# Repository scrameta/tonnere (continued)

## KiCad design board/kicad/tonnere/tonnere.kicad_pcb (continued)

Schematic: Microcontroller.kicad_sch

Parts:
BT1: CR2032; BAT-TH_BS-05-A1BJ001; Manufacturer Part BS-05-A1BJ001; JLC_3DModel 65806d021c214524b18c90626aa24a1f
C11, C21, C31, C33, C35, C36, C37, C41, C45, C54, C58, C63, C68, C70: 0.1uF; C_0603_1608Metric; LCSC C14663
C16, C19: 22pF; C_0603_1608Metric; LCSC C1653
C17, C18: 16pF; C_0603_1608Metric; LCSC C327125
C22, C23, C50: 4.7uF; C_0603_1608Metric; LCSC C19666
C25, C26: 18pF; C_0603_1608Metric; LCSC C1647
C29: 1uF; C_0805_2012Metric; LCSC C28323
C66, C67: 2.2uF; C_0603_1608Metric; LCSC C23630
D6: 1N4148WS; D_SOD-323; LCSC C2128
FB1: 70@100MHz; L_0805_2012Metric; LCSC C1012
J8: STM GPIO; PinSocket_1x07_P2.54mm_Vertical; LCSC C225482
J9: STM SWD; PinHeader_1x05_P2.54mm_Vertical; LCSC C225480
J26: I2C; PinHeader_2x02_P2.54mm_Vertical; LCSC C225517
JP1: STM BOOT0; PinHeader_1x03_P2.54mm_Vertical; LCSC C49257
Q3: 2N7002; SOT-23; LCSC C8545
R4, R5: 5k1; R_0603_1608Metric; LCSC C23186
R7, R57: 1k; R_0603_1608Metric; LCSC C21190
R8, R37, R39: 1m; R_0603_1608Metric; LCSC C22935
R31, R58, R63: 10k; R_0603_1608Metric; LCSC C25804
R42: 12K 1%; R_0603_1608Metric; LCSC C22790
R54: 100k; R_0603_1608Metric; LCSC C25803
R56: 820; R_0603_1608Metric; LCSC C23253
R60: 0; R_0603_1608Metric; LCSC C21189; not fitted
R64, R84, R85: 22; R_0603_1608Metric; LCSC C23345
R68, R69: 4k7; R_0603_1608Metric; LCSC C23162
RN7, RN10: 22; R_Array_Convex_4x0603; LCSC C12008
SW2: USB HS/FS; SW-SMD_MST22D18G2; JLC_3DModel a98562e0d24740e1809e54f73242e180
U5: TPD4E02B04DQA; USON-10_2.5x1.0mm_P0.5mm; LCSC C106794
U12: 74LVC1G17; SOT-23-5; LCSC C7836
U18, U22: FSUSB42UMX-TP; XQFN-10_L1.8-W1.4-P0.40-TL; Manufacturer Part FSUSB42UMX-TP; JLC_3DModel ba08a50be60c45c893f1ed2ee1dbd52d
U21: USB3300-EZK; QFN-32-1EP_5x5mm_P0.5mm_EP3.45x3.45mm; LCSC C108383
U25: STM32F407ZGTx; LQFP-144_20x20mm_P0.5mm; LCSC C36869
U27: PCA9546APWR; TSSOP-16_L5.0-W4.4-P0.65-LS6.4-BL; Manufacturer Part PCA9546APWR; JLC_3DModel 534f03d8fe164fbab551f91e5a792e30
USB2: TYPE-C 14P CC-2.6; TYPE-C-TH_TYPE-C-14P-CC-2.6; MPN TYPE-C 14P CC-2.6; LCSC Part C5187475
Y1: 24MHz; Crystal_SMD_3225-4Pin_3.2x2.5mm; LCSC C5122304
Y2: 8MHz; Crystal_SMD_3225-4Pin_3.2x2.5mm; LCSC C2924617
Y3: 32.768KHz; Crystal_SMD_3215-2Pin_3.2x1.5mm; LCSC C32346

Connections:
+3V3: C31.1, C33.1, C36.1, C41.1, C45.1, C54.1, C58.1, C63.1, C68.1, C70.1, FB1.1, J8.1, J9.1, J26.1, R31.1, R68.1, R69.1, SW2.1 (A), U12.5 (VCC), U18.9 (VCC), U21.6 (VDD3.3), U21.16 (VDD3.3), U21.25 (VDD3.3), U21.30 (VDD3.3), U21.31 (REG_EN), U22.9 (VCC), U25.17 (VDD), U25.30 (VDD), U25.39 (VDD), U25.52 (VDD), U25.62 (VDD), U25.72 (VDD), U25.84 (VDD), U25.95 (VDD), U25.108 (VDD), U25.121 (VDD), U25.131 (VDD), U25.143 (PDR_ON), U25.144 (VDD), U27.16 (VCC); also elsewhere on the board
+3VA3_STM: C29.1, C37.1, FB1.2, U25.32 (VREF+), U25.33 (VDDA); also elsewhere on the board
+5V: SW2.4 (A); also elsewhere on the board
/AtariInterfaces/JOY2.POT4: U25.22 (PF10); also elsewhere on the board
/AtariInterfaces/JOY2.POT5: U25.27 (PC1); also elsewhere on the board
/AtariInterfaces/JOY2.POT6: U25.34 (PA0); also elsewhere on the board
/AtariInterfaces/JOY2.POT7: U25.35 (PA1); also elsewhere on the board
/AtariInterfaces/JOY.POT0: U25.18 (PF6); also elsewhere on the board
/AtariInterfaces/JOY.POT1: U25.19 (PF7); also elsewhere on the board
/AtariInterfaces/JOY.POT2: U25.20 (PF8); also elsewhere on the board
/AtariInterfaces/JOY.POT3: U25.21 (PF9); also elsewhere on the board
/Audio/STMAUD.ADC.L: U25.42 (PA6); also elsewhere on the board
/Audio/STMAUD.ADC.PBI: U25.44 (PC4); also elsewhere on the board
/Audio/STMAUD.ADC.R: U25.40 (PA4); also elsewhere on the board
/Audio/STMAUD.ADC.SIO: U25.45 (PC5); also elsewhere on the board
/ESP32/ESP.BOOT: U25.91 (PG6); also elsewhere on the board
/ESP32/ESP.EN: U25.92 (PG7); also elsewhere on the board
/ESP32/ESP.SGPI0: U25.93 (PG8); also elsewhere on the board
/ESP32/ESP.SGPI1: U25.124 (PG9); also elsewhere on the board
/ESP32/ESP.SGPI2: U25.125 (PG10); also elsewhere on the board
/ESP32/ESP.SGPIO: U25.100 (PA8); also elsewhere on the board
/ESP32/UART1.RX: U25.97 (PC7); also elsewhere on the board
/ESP32/UART1.TX: U25.96 (PC6); also elsewhere on the board
/FPGA/FPGA.CONFIG_N: U25.128 (PG13); also elsewhere on the board
/FPGA/FPGA.CONF_DONE: U25.132 (PG15); also elsewhere on the board
/FPGA/FPGA.IRQ: U25.127 (PG12); also elsewhere on the board
/FPGA/FPGA.PS_N: U25.126 (PG11); also elsewhere on the board
/FPGA/FPGA.STATUS_N: U25.129 (PG14); also elsewhere on the board
/FPGA/FSMC.A0: U25.10 (PF0); also elsewhere on the board
/FPGA/FSMC.A1: U25.11 (PF1); also elsewhere on the board
/FPGA/FSMC.A2: U25.12 (PF2); also elsewhere on the board
/FPGA/FSMC.A3: U25.13 (PF3); also elsewhere on the board
/FPGA/FSMC.A4: U25.14 (PF4); also elsewhere on the board
/FPGA/FSMC.A5: U25.15 (PF5); also elsewhere on the board
/FPGA/FSMC.A6: U25.50 (PF12); also elsewhere on the board
/FPGA/FSMC.A7: U25.53 (PF13); also elsewhere on the board
/FPGA/FSMC.A8: U25.54 (PF14); also elsewhere on the board
/FPGA/FSMC.A9: U25.55 (PF15); also elsewhere on the board
/FPGA/FSMC.A10: U25.56 (PG0); also elsewhere on the board
/FPGA/FSMC.A11: U25.57 (PG1); also elsewhere on the board
/FPGA/FSMC.A12: U25.87 (PG2); also elsewhere on the board
/FPGA/FSMC.A13: U25.88 (PG3); also elsewhere on the board
/FPGA/FSMC.A14: U25.89 (PG4); also elsewhere on the board
/FPGA/FSMC.A15: U25.90 (PG5); also elsewhere on the board
/FPGA/FSMC.A16: U25.80 (PD11); also elsewhere on the board
/FPGA/FSMC.A17: U25.81 (PD12); also elsewhere on the board
/FPGA/FSMC.A18: U25.82 (PD13); also elsewhere on the board
/FPGA/FSMC.A19: U25.2 (PE3); also elsewhere on the board
/FPGA/FSMC.A20: U25.3 (PE4); also elsewhere on the board
/FPGA/FSMC.A21: U25.4 (PE5); also elsewhere on the board
/FPGA/FSMC.A22: U25.5 (PE6); also elsewhere on the board
/FPGA/FSMC.D0: U25.85 (PD14); also elsewhere on the board
/FPGA/FSMC.D1: U25.86 (PD15); also elsewhere on the board
/FPGA/FSMC.D2: U25.114 (PD0); also elsewhere on the board
/FPGA/FSMC.D3: U25.115 (PD1); also elsewhere on the board
/FPGA/FSMC.D4: U25.58 (PE7); also elsewhere on the board
/FPGA/FSMC.D5: U25.59 (PE8); also elsewhere on the board
/FPGA/FSMC.D6: U25.60 (PE9); also elsewhere on the board
/FPGA/FSMC.D7: U25.63 (PE10); also elsewhere on the board
/FPGA/FSMC.D8: U25.64 (PE11); also elsewhere on the board
/FPGA/FSMC.D9: U25.65 (PE12); also elsewhere on the board
/FPGA/FSMC.D10: U25.66 (PE13); also elsewhere on the board
/FPGA/FSMC.D11: U25.67 (PE14); also elsewhere on the board
/FPGA/FSMC.D12: U25.68 (PE15); also elsewhere on the board
/FPGA/FSMC.D13: U25.77 (PD8); also elsewhere on the board
/FPGA/FSMC.D14: U25.78 (PD9); also elsewhere on the board
/FPGA/FSMC.D15: U25.79 (PD10); also elsewhere on the board
/FPGA/FSMC.NBL0: U25.141 (PE0); also elsewhere on the board
/FPGA/FSMC.NBL1: U25.142 (PE1); also elsewhere on the board
/FPGA/FSMC.NE1: U25.123 (PD7); also elsewhere on the board
/FPGA/FSMC.NOE: U25.118 (PD4); also elsewhere on the board
/FPGA/FSMC.NWAIT: U25.122 (PD6); also elsewhere on the board
/FPGA/FSMC.NWE: U25.119 (PD5); also elsewhere on the board
/FPGA/HDMI.SCL: U27.5 (SC0); also elsewhere on the board
/FPGA/HDMI.SDA: U27.4 (SD0); also elsewhere on the board
/FPGA/PLL.SCL1: U27.10 (SC2); also elsewhere on the board
/FPGA/PLL.SCL2: U27.12 (SC3); also elsewhere on the board
/FPGA/PLL.SDA1: U27.9 (SD2); also elsewhere on the board
/FPGA/PLL.SDA2: U27.11 (SD3); also elsewhere on the board
/FPGA/SPI.CS1: U25.136 (PB6); also elsewhere on the board
/FPGA/SPI.CS2: U25.137 (PB7); also elsewhere on the board
/FPGA/SPI.MISO: U25.134 (PB4); also elsewhere on the board
/FPGA/SPI.MOSI: U25.43 (PA7); also elsewhere on the board
/FPGA/SPI.SCK: R64.2; also elsewhere on the board
/IOCards/SD.CK: RN7.4 (R4.1); also elsewhere on the board
/IOCards/SD.CMD: RN7.1 (R1.1); also elsewhere on the board
/IOCards/SD.D0: RN10.4 (R4.1); also elsewhere on the board
/IOCards/SD.D1: RN10.3 (R3.1); also elsewhere on the board
/IOCards/SD.D2: RN10.2 (R2.1); also elsewhere on the board
/IOCards/SD.D3: RN10.1 (R1.1); also elsewhere on the board
/IOCards/SD.DETECT: RN7.3 (R3.1); also elsewhere on the board
/IOCards/SD.WP: RN7.2 (R2.1); also elsewhere on the board
/Microcontroller/1V8: C22.1, U21.15 (VDD1.8), U21.26 (VDD1.8)
/Microcontroller/1VA8: C23.1, U21.29 (VDDA1.8)
/Microcontroller/+3V_BAT: BT1.1, C35.1, U25.6 (VBAT)
/Microcontroller/+V5_VBUS_FOR_DETECT: R7.1, SW2.6 (C), USB2.A4 (VBUS), USB2.A9 (VBUS), USB2.B4 (VBUS), USB2.B9 (VBUS)
/Microcontroller/BOOT1: R63.1, U25.48 (PB2)
/Microcontroller/NRST: C11.1, J9.5, Q3.3 (D), R31.2, U25.25 (NRST)
/Microcontroller/Net-(C20-Pad1): C21.1, R57.1, U12.4
/Microcontroller/Net-(C49-Pad1): C50.1, R56.2, SW2.5 (B)
/Microcontroller/Net-(J9-Pin_4): J8.4, U25.75 (PB14)
/Microcontroller/Net-(J9-Pin_5): J8.5, U25.76 (PB15)
/Microcontroller/Net-(J9-Pin_6): J8.6, U25.110 (PA15)
/Microcontroller/Net-(J9-Pin_7): J8.7, U25.1 (PE2)
/Microcontroller/Net-(J10-Pin_2): J9.2, U25.105 (PA13)
/Microcontroller/Net-(J10-Pin_3): J9.3, U25.109 (PA14)
/Microcontroller/Net-(J27-Pin_3): J26.3, U27.7 (SC1)
/Microcontroller/Net-(J27-Pin_4): J26.4, U27.6 (SD1)
/Microcontroller/Net-(U17-D+): U5.2 (IO2), U18.1 (D+), USB2.A6 (DP1), USB2.B6 (DP2)
/Microcontroller/Net-(U17-D-): U5.1 (IO1), U18.2 (D-), USB2.A7 (DN1), USB2.B7 (DN2)
/Microcontroller/Net-(U17-SEL): SW2.2 (B), U18.10 (SEL), U22.10 (SEL)
/Microcontroller/Net-(U20-RBIAS): R42.1, U21.32 (RBIAS)
/Microcontroller/Net-(U20-RESET): R60.1, U21.9 (RESET)
/Microcontroller/Net-(U20-VBUS): R56.1, U21.4 (VBUS)
/Microcontroller/Net-(U20-XI): C19.2, R37.2, U21.28 (XI), Y1.1
/Microcontroller/Net-(U20-XO): C16.2, R37.1, U21.27 (XO), Y1.3
/Microcontroller/Net-(U23-PA11): R84.1, U25.103 (PA11)
/Microcontroller/Net-(U23-PA12): R85.1, U25.104 (PA12)
/Microcontroller/Net-(U23-PB3): R64.1, U25.133 (PB3)
/Microcontroller/Net-(U23-PC14): C26.2, U25.8 (PC14), Y3.1
/Microcontroller/Net-(U23-PC15): C25.2, U25.9 (PC15), Y3.2
/Microcontroller/Net-(U23-PH0): C18.2, R39.1, U25.23 (PH0), Y2.3
/Microcontroller/Net-(U23-PH1): C17.2, R39.2, U25.24 (PH1), Y2.1
/Microcontroller/Net-(U23-VCAP_1): C66.1, U25.71 (VCAP_1)
/Microcontroller/Net-(U23-VCAP_2): C67.1, U25.106 (VCAP_2)
/Microcontroller/Net-(USB1-CC1): R4.1, USB2.A5 (CC1)
/Microcontroller/Net-(USB1-CC2): R5.1, USB2.B5 (CC2)
/Microcontroller/STM.I2CRESET: U25.49 (PF11), U27.3 (RESET#)
/Microcontroller/STM.SCL: R69.2, U25.139 (PB8), U27.14 (SCL)
/Microcontroller/STM.SDA: R68.2, U25.140 (PB9), U27.15 (SDA)
/Microcontroller/STMUSB.DM1: R84.2, U18.4 (HSD1-), U22.6 (HSD2-)
/Microcontroller/STMUSB.DM2: U18.6 (HSD2-), U21.8 (DM), U22.4 (HSD1-)
/Microcontroller/STMUSB.DP1: R85.2, U18.5 (HSD1+), U22.7 (HSD2+)
/Microcontroller/STMUSB.DP2: U18.7 (HSD2+), U21.7 (DP), U22.5 (HSD1+)
/Microcontroller/USART1.RX: U25.102 (PA10); also elsewhere on the board
/Microcontroller/USART1.TX: U25.101 (PA9); also elsewhere on the board
/Microcontroller/USB.DM: U22.2 (D-); also elsewhere on the board
/Microcontroller/USB.DP: U22.1 (D+); also elsewhere on the board
/Microcontroller/USBPHY.CLK: U21.14 (CLKOUT), U25.41 (PA5)
/Microcontroller/USBPHY.D0: U21.24 (DATA0), U25.37 (PA3)
/Microcontroller/USBPHY.D1: U21.23 (DATA1), U25.46 (PB0)
/Microcontroller/USBPHY.D2: U21.22 (DATA2), U25.47 (PB1)
/Microcontroller/USBPHY.D3: U21.21 (DATA3), U25.69 (PB10)
/Microcontroller/USBPHY.D4: U21.20 (DATA4), U25.70 (PB11)
/Microcontroller/USBPHY.D5: U21.19 (DATA5), U25.73 (PB12)
/Microcontroller/USBPHY.D6: U21.18 (DATA6), U25.74 (PB13)
/Microcontroller/USBPHY.D7: U21.17 (DATA7), U25.135 (PB5)
/Microcontroller/USBPHY.DIR: U21.12 (DIR), U25.28 (PC2)
/Microcontroller/USBPHY.NXT: U21.11 (NXT), U25.29 (PC3)
/Microcontroller/USBPHY.STP: U21.13 (STP), U25.26 (PC0)
/Microcontroller/unconnected-(J9-Pin_3-Pad3): J8.3
/Microcontroller/unconnected-(U4-IO3-Pad4): U5.4 (IO3)
/Microcontroller/unconnected-(U4-IO4-Pad5): U5.5 (IO4)
/Microcontroller/unconnected-(U4-NC-Pad6): U5.6 (NC)
/Microcontroller/unconnected-(U4-NC-Pad7): U5.7 (NC)
/Microcontroller/unconnected-(U4-NC-Pad9): U5.9 (NC)
/Microcontroller/unconnected-(U4-NC-Pad10): U5.10 (NC)
/Microcontroller/unconnected-(U20-CPEN-Pad3): U21.3 (CPEN)
/Microcontroller/unconnected-(U20-EXTVBUS-Pad10): U21.10 (EXTVBUS)
/Microcontroller/unconnected-(U20-ID-Pad5): U21.5 (ID)
GND: BT1.2, C11.2, C16.1, C17.1, C18.1, C19.1, C22.2, C23.2, C25.1, C26.1, C31.2, C33.2, C35.2, C36.2, C41.2, C45.2, C50.2, C54.2, C58.2, C63.2, C66.2, C67.2, C68.2, C70.2, D6.2 (A), J8.2, J9.4, J26.2, Q3.2 (S), R4.2, R5.2, R8.2, R42.2, R54.2, R58.1, R60.2, R63.2, SW2.3 (C), U5.3 (G), U5.8 (G), U12.3 (GND), U18.3 (GND), U18.8 (OE#), U21.1 (GND), U21.2 (GND), U21.33 (GND), U22.3 (GND), U22.8 (OE#), U25.16 (VSS), U25.36 (PA2), U25.38 (VSS), U25.51 (VSS), U25.61 (VSS), U25.83 (VSS), U25.94 (VSS), U25.107 (VSS), U25.120 (VSS), U25.130 (VSS), U27.1 (A0), U27.2 (A1), U27.8 (GND), U27.13 (A2), USB2.A1 (GND), USB2.A12 (GND), USB2.B1 (GND), USB2.B12 (GND), USB2.SH1, USB2.SH2, Y1.2, Y1.4, Y2.2, Y2.4; also elsewhere on the board
GNDA: C29.2, C37.2, U25.31 (VSSA); also elsewhere on the board
unnamed: C21.2, D6.1 (K), Q3.1 (G), R54.1
unnamed: JP1.1 (A), R58.2
unnamed: JP1.3 (B), R57.2
unnamed: JP1.2 (C), U25.138 (BOOT0)
unnamed: R7.2, R8.1, U12.2
unnamed: RN7.8 (R1.2), U25.116 (PD2)
unnamed: RN7.7 (R2.2), U25.117 (PD3)
unnamed: RN7.6 (R3.2), U25.7 (PC13)
unnamed: RN7.5 (R4.2), U25.113 (PC12)
unnamed: RN10.8 (R1.2), U25.112 (PC11)
unnamed: RN10.7 (R2.2), U25.111 (PC10)
unnamed: RN10.6 (R3.2), U25.99 (PC9)
unnamed: RN10.5 (R4.2), U25.98 (PC8)

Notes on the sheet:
ADCDUMMY
H:D2, L:D1 So H=HS_EXT,LS_HUB L=LS_EXT,HS_HUB
With pull up via 10k to 3.3v
Downstream pull ups on other sheets
Automatic DFU mode on VBUS connect - sends 10ms reset pulse on NSRT on connect.
OK to share with VDAC?

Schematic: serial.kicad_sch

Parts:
J13: STM USART TTL; PinSocket_1x03_P2.54mm_Vertical; LCSC C49257

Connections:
/Microcontroller/USART1.RX: J13.3; also elsewhere on the board
/Microcontroller/USART1.TX: J13.2; also elsewhere on the board
GND: J13.1; also elsewhere on the board

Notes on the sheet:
TTL USART for debugging

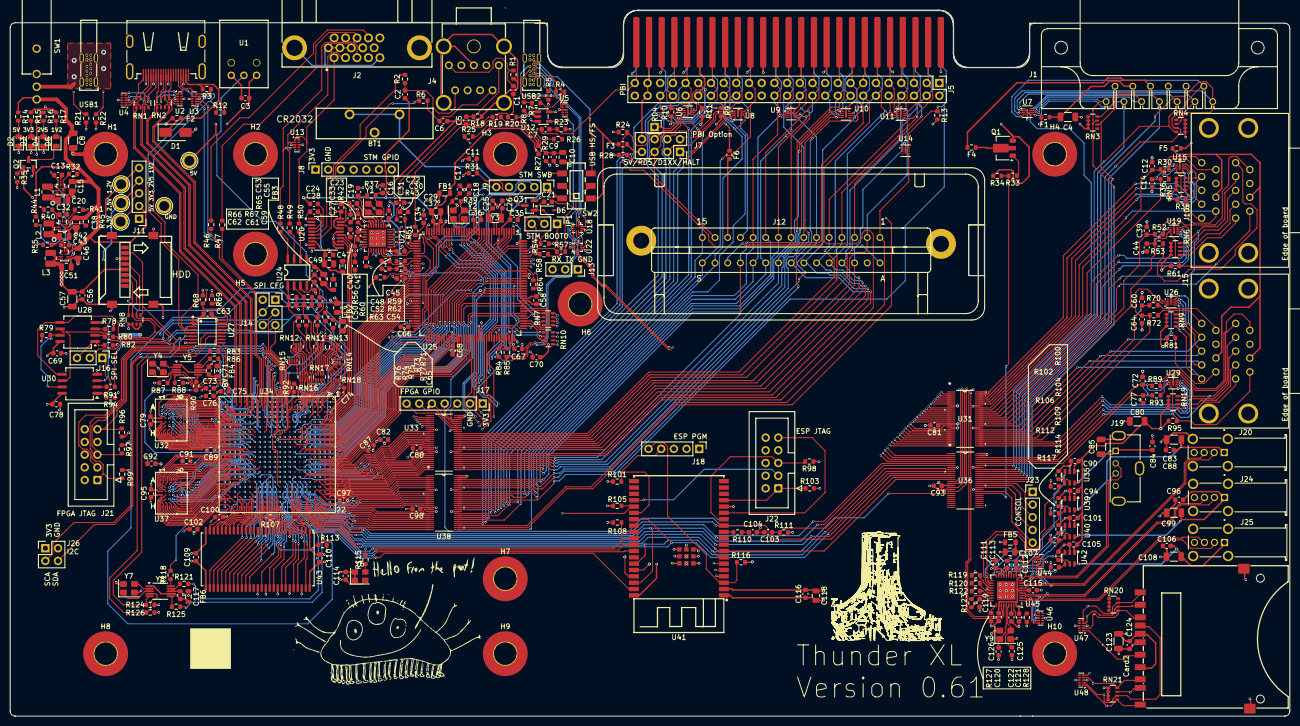
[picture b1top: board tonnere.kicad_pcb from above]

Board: 6 copper layers, 256.2 x 141.3 mm, 406 parts (0 on the bottom side), 655 nets.

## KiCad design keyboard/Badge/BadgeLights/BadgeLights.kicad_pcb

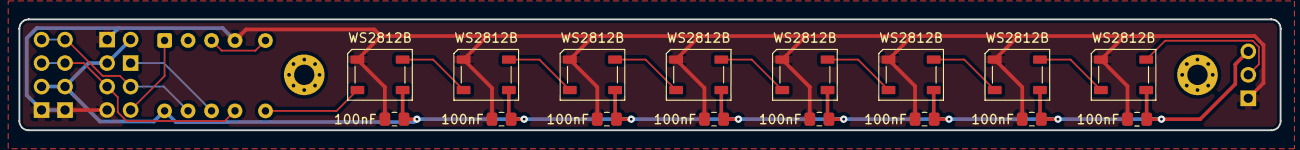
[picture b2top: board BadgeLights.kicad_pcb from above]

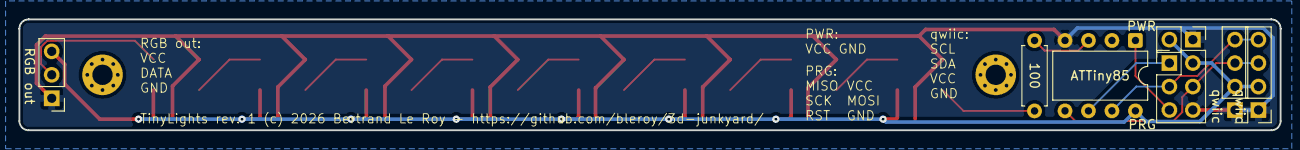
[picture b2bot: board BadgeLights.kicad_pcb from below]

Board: 2 copper layers, 136.5 x 12.0 mm, 25 parts (7 on the bottom side), 16 nets.

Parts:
C24, C25, C26, C27, C28, C29, C30, C31: 100nF; C_0805_2012Metric_Pad1.18x1.45mm_HandSolder
D1, D2, D3, D4, D5, D6, D7, D8: WS2812B; LED_WS2812B_PLCC4_5.0x5.0mm_P3.2mm
H1, H2: MountingHole_Pad; MountingHole_2.2mm_M2_Pad_Via
PRG: Conn_02x03_Odd_Even; PinHeader_2x03_P2.54mm_Vertical
PWR: Conn_01x02_Pin; PinHeader_1x02_P2.54mm_Vertical
R1: R; R_Axial_DIN0207_L6.3mm_D2.5mm_P7.62mm_Horizontal
RGB out: Conn_01x03_Pin; PinHeader_1x03_P2.54mm_Vertical
U1: ATtiny85-20P; DIP-8_W7.62mm
qwiic: Conn_01x04; PinHeader_1x04_P2.54mm_Vertical
qwiic#2: Conn_01x04; PinHeader_1x04_P2.54mm_Vertical

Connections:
+5V: C24.1, C25.1, C26.1, C27.1, C28.1, C29.1, C30.1, C31.1, D1.1 (VDD), D2.1 (VDD), D3.1 (VDD), D4.1 (VDD), D5.1 (VDD), D6.1 (VDD), D7.1 (VDD), D8.1 (VDD), PRG.2, PWR.2, RGB out.3, U1.8 (VCC), qwiic.2, qwiic#2.2
GND: C24.2, C25.2, C26.2, C27.2, C28.2, C29.2, C30.2, C31.2, D1.3 (VSS), D2.3 (VSS), D3.3 (VSS), D4.3 (VSS), D5.3 (VSS), D6.3 (VSS), D7.3 (VSS), D8.3 (VSS), PRG.6, PWR.1, RGB out.1, U1.4 (GND), qwiic.1, qwiic#2.1
unnamed: D1.4 (DIN), R1.2
unnamed: D1.2 (DOUT), D2.4 (DIN)
unnamed: D2.2 (DOUT), D3.4 (DIN)
unnamed: D3.2 (DOUT), D4.4 (DIN)
unnamed: D4.2 (DOUT), D5.4 (DIN)
unnamed: D5.2 (DOUT), D6.4 (DIN)
unnamed: D6.2 (DOUT), D7.4 (DIN)
unnamed: D7.2 (DOUT), D8.4 (DIN)
unnamed: D8.2 (DOUT), RGB out.2
unnamed: PRG.1, U1.6 (PB1)
unnamed: PRG.3, U1.7 (PB2), qwiic.4, qwiic#2.4
unnamed: PRG.4, U1.5 (AREF/PB0), qwiic.3, qwiic#2.3
unnamed: PRG.5, U1.1 (~RESET/PB5)
unnamed: R1.1, U1.3 (XTAL2/PB4)

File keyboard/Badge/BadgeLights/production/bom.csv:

Designator,Footprint,Quantity,Value,LCSC Part #
"C24, C25, C26, C27, C28, C29, C30, C31",0805,8,100nF,
"D1, D2, D3, D4, D5, D6, D7, D8",LED_WS2812B_PLCC4_5.0x5.0mm_P3.2mm,8,WS2812B,
PRG,PinHeader_2x03_P2.54mm_Vertical,1,Conn_02x03_Odd_Even,
PWR,PinHeader_1x02_P2.54mm_Vertical,1,Conn_01x02_Pin,
"QWIIC_2, QWIIC",PinHeader_1x04_P2.54mm_Vertical,2,Conn_01x04,
R1,R_Axial_DIN0207_L6.3mm_D2.5mm_P7.62mm_Horizontal,1,R,
RGB OUT,PinHeader_1x03_P2.54mm_Vertical,1,Conn_01x03_Pin,
U1,DIP-8_W7.62mm,1,ATtiny85-20P,

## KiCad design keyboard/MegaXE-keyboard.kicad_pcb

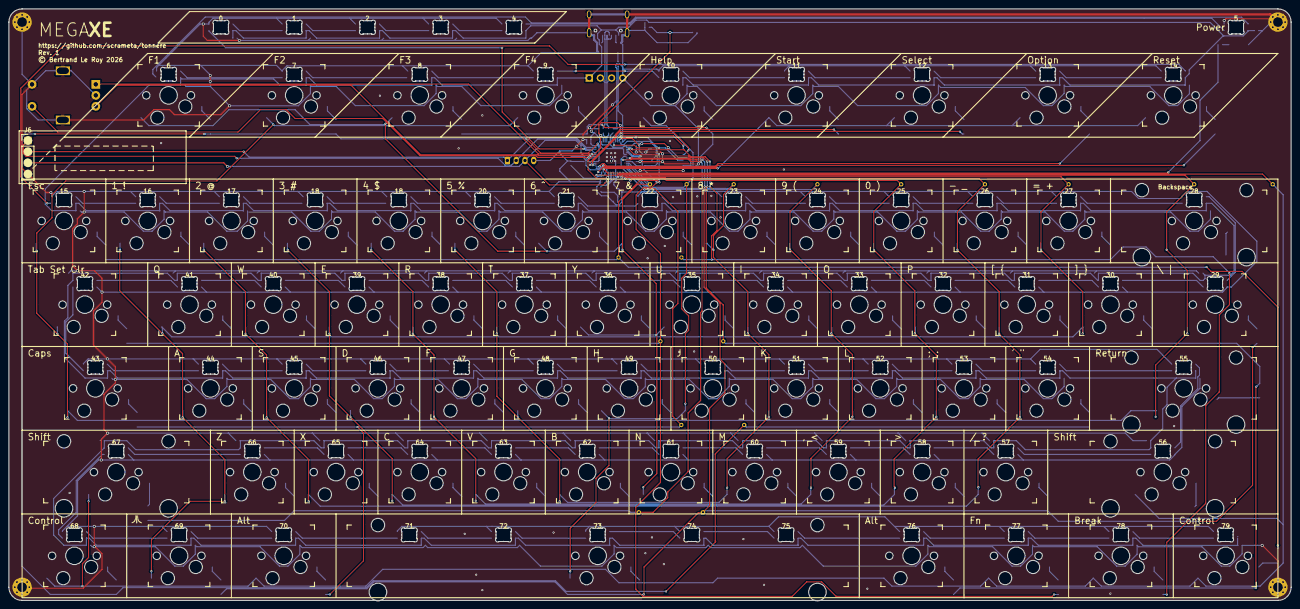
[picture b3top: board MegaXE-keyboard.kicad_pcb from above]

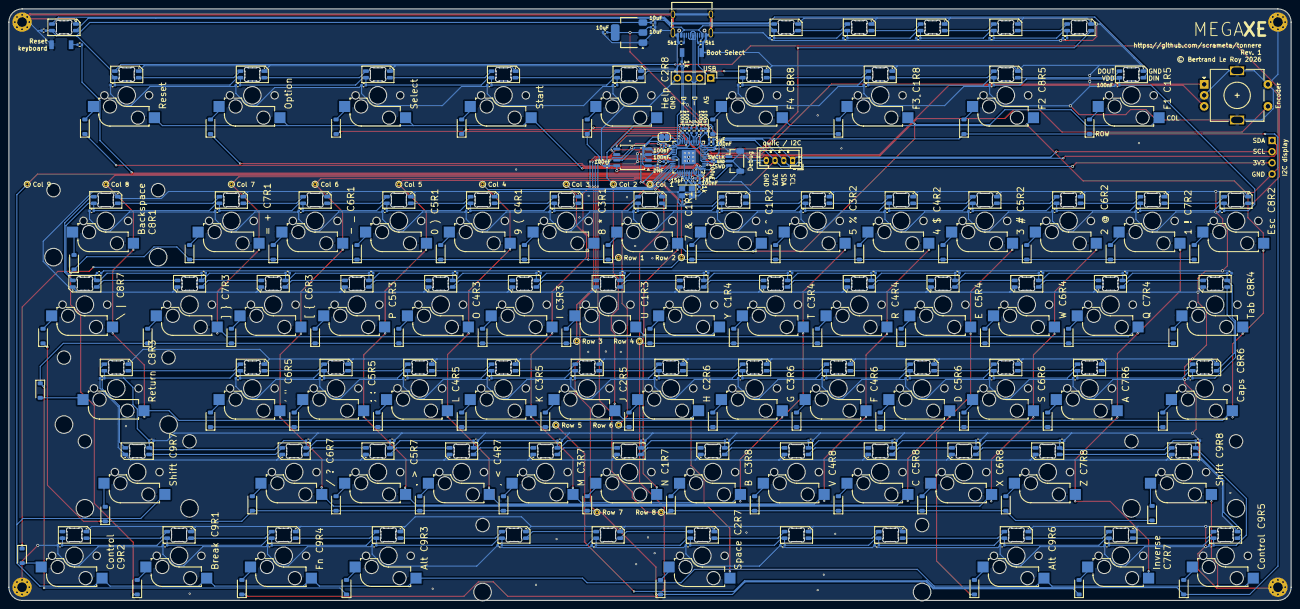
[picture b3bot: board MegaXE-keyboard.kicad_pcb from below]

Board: 2 copper layers, 291.8 x 134.6 mm, 359 parts (288 on the bottom side), 202 nets.

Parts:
C4, C6, C7, C8, C9, C10, C11, C12, C13, C42, C75, C76, C77, C78, C79, C80, C81, C82, C83, C84, C85, C86, C87, C88, C89, C90, C91, C92, C93, C94, C95, C96, C97, C98, C99, C100, C101, C102, C103, C104, C105, C106, C107, C108, C109, C110, C111, C112, C113, C114, C115, C116, C117, C118, C119, C120, C121, C123, C124, C125, C126, C127, C128, C129, C130, C131, C132, C133, C134, C135, C136, C137, C138, C139, C140, C141, C142, C143, C144, C145, C146, C147, C148, C149, C150, C151, C152, C153, C154, C155: 100nF; C_0402_1005Metric
C5, C14: 1uF; C_0402_1005Metric
C24, C25: 15pF; C_0402_1005Metric
C27, C28, C43: 10uF; C_0402_1005Metric
D17, D18, D19, D20, D21, D22, D23, D24, D25, D26, D27, D28, D29, D30, D31, D47, D49, D51, D53, D55, D57, D59, D61, D63, D65, D67, D69, D71, D73, D75, D77, D79, D81, D83, D85, D87, D89, D91, D93, D95, D97, D99, D101, D103, D105, D107, D109, D111, D113, D115, D119, D121, D123, D125, D127, D128, D129, D130, D131, D132, D133, D134, D135, D137, D139, D141, D143, D145, D147, D148: 1N4148W; D_SOD-123
D149, D150, D151, D152, D153, D154, D155, D156, D157, D158, D159, D160, D161, D162, D163, D164, D165, D166, D167, D168, D169, D170, D171, D172, D173, D174, D175, D176, D177, D178, D179, D180, D181, D182, D183, D184, D185, D186, D187, D188, D189, D190, D191, D192, D193, D194, D195, D197, D198, D199, D200, D201, D202, D203, D204, D205, D206, D207, D208, D209, D210, D211, D212, D213, D214, D215, D216, D217, D218, D219, D220, D221, D222, D223, D224, D225, D226, D227, D228, D229: SK6812MINI; LED_SK6812MINI-E_3.2x2.8mm_P1.5mm_ReverseMount
H1, H2, H3, H4: MountingHole_Pad; MountingHole_2.2mm_M2_Pad_Via
J1: Conn_01x04_Socket; JST_PH_B4B-PH-K_1x04_P2.00mm_Vertical
J4: Conn_01x04_Pin; PinHeader_1x04_P2.54mm_Vertical
J5: USB_C_Receptacle_USB2.0_16P; USB_C_Receptacle_C2765186
J6: Conn_01x04; PinHeader_1x04_P2.54mm_Vertical
J9: SM03B-SRSS-TB; JST_SH_BM03B-SRSS-TB_1x03-1MP_P1.00mm_Vertical
R6, R7: 5k1; R_0402_1005Metric
R26, R28: 27; R_0402_1005Metric
R30, R31, R32: 1k; R_0402_1005Metric
R36: DNF; R_0402_1005Metric
R37: 0; SolderJumper-2_P1.3mm_Bridged_RoundedPad1.0x1.5mm
SW1: RotaryEncoder_Switch; RotaryEncoder_Alps_EC11E-Switch_Vertical_H20mm
SW2: SW_BOOT_SELECT; TactileSwitch
SW3: SW_RESET; TactileSwitch
SW10, SW11, SW12, SW13, SW14, SW15, SW16, SW17, SW19, SW20, SW21, SW22, SW23, SW24, SW25, SW26, SW27, SW28, SW29, SW30, SW31, SW32, SW33, SW34, SW35, SW36, SW37, SW38, SW39, SW40, SW41, SW42, SW43, SW44, SW45, SW46, SW47, SW48, SW49, SW50, SW51, SW52, SW53, SW54, SW55, SW56, SW57, SW58, SW59, SW61, SW64, SW65, SW66, SW67, SW68, SW70, SW71, SW72, SW73, SW74, SW76, SW77, SW78, SW79, SW80: MX; Kailh_socket_MX_1-00U
SW18: MX; Kailh_socket_MX_6-25U
SW62, SW63, SW69, SW75: MX; Kailh_socket_MX_2-00U
TP1, TP2, TP3, TP4, TP5, TP6, TP7, TP8, TP9, TP10, TP11, TP12, TP13, TP14, TP15, TP16, TP17: TestPoint; TestPoint_THTPad_D1.0mm_Drill0.5mm
U4: NCP1117-3.3; SOT-223-3_TabPin2
U7: RP2040; QFN-56-1EP_7x7mm_P0.4mm_EP3.2x3.2mm
U9: W25Q128JVS; SOIC-8_5.3x5.3mm_P1.27mm
X1: 12MHz; Crystal_SMD_Abracon_ABM8AIG-4Pin_3.2x2.5mm

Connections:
+1V1: C4.1, C5.1, C6.1, U7.23 (DVDD), U7.45 (VREG_VOUT), U7.50 (DVDD)
+3V3: C7.1, C8.1, C9.1, C10.1, C11.1, C12.1, C13.1, C14.1, C27.1, C28.1, C42.1, J1.3, J6.3, R36.1, U4.2 (VO), U7.1 (IOVDD), U7.10 (IOVDD), U7.22 (IOVDD), U7.33 (IOVDD), U7.42 (IOVDD), U7.43 (ADC_AVDD), U7.44 (VREG_IN), U7.48 (USB_VDD), U7.49 (IOVDD), U9.8 (VCC)
/Controller/FLASH_SS: R36.2, R37.2, U9.1 (~CS)
/Controller/QSPI_SCLK: U7.52 (QSPI_SCLK), U9.6 (CLK)
/Controller/QSPI_SD0: U7.53 (QSPI_SD0), U9.5 (DI(IO0))
/Controller/QSPI_SD1: U7.55 (QSPI_SD1), U9.2 (DO(IO1))
/Controller/QSPI_SD2: U7.54 (QSPI_SD2), U9.3 (IO2)
/Controller/QSPI_SD3: U7.51 (QSPI_SD3), U9.7 (IO3)
/Controller/QSPI_SS: R30.1, R37.1, U7.56 (QSPI_SS)
/Controller/SCL: J1.1, J6.2, U7.41 (GPIO29_ADC3)
/Controller/SDA: J1.2, J6.1, U7.40 (GPIO28_ADC2)
/Controller/SWCLK: J9.1, U7.24 (SWCLK)
/Controller/SWD: J9.3, U7.25 (SWD)
/Controller/USB_D+: J4.3, J5.A6 (D+), J5.B6 (D+), R26.1
/Controller/USB_D-: J4.2, J5.A7 (D-), J5.B7 (D-), R28.1
/Controller/USB_DN: R28.2, U7.46 (USB_DM)
/Controller/USB_DP: R26.2, U7.47 (USB_DP)
/Controller/XIN: C24.1, U7.20 (XIN), X1.1
/Controller/XOUT: R31.2, U7.21 (XOUT)
/Controller/~USB_BOOT: R30.2, SW2.2
/Key0/RGB_IN: D169.4 (DOUT), D178.2 (DIN)
/Key0/RGB_OUT: D178.4 (DOUT), D185.2 (DIN)
/Key1/RGB_IN: D193.2 (DIN), D201.4 (DOUT)
/Key1/RGB_OUT: D186.2 (DIN), D193.4 (DOUT)
/Key2/RGB_OUT: D177.2 (DIN), D186.4 (DOUT)
/Key3/RGB_OUT: D170.2 (DIN), D177.4 (DOUT)
/Key4/RGB_OUT: D167.2 (DIN), D170.4 (DOUT)
/Key5/RGB_OUT: D151.2 (DIN), D167.4 (DOUT)
/Key6/RGB_OUT: D150.2 (DIN), D151.4 (DOUT)
/Key7/RGB_OUT: D150.4 (DOUT), D168.2 (DIN)
/Key8/RGB_OUT: D168.4 (DOUT), D169.2 (DIN)
/KeyA/RGB_IN: D197.2 (DIN), D202.4 (DOUT)
/KeyA/RGB_OUT: D188.2 (DIN), D197.4 (DOUT)
/KeyAlt/RGB_IN: D198.4 (DOUT), D227.2 (DIN)
/KeyAlt/RGB_OUT: D221.2 (DIN), D227.4 (DOUT)
/KeyB/RGB_IN: D155.4 (DOUT), D161.2 (DIN)
/KeyB/RGB_OUT: D161.4 (DOUT), D176.2 (DIN)
/KeyBackslash/RGB_IN: D204.4 (DOUT), D229.2 (DIN)
/KeyBackslash/RGB_OUT: D194.2 (DIN), D229.4 (DOUT)
/KeyBreak/RGB_IN: D210.2 (DIN), D226.4 (DOUT)
/KeyBreak/RGB_OUT: D210.4 (DOUT), D225.2 (DIN)
/KeyC/RGB_IN: D176.4 (DOUT), D184.2 (DIN)
/KeyC/RGB_OUT: D184.4 (DOUT), D187.2 (DIN)
/KeyCaps/RGB_IN: D202.2 (DIN), D206.4 (DOUT)
/KeyComma/RGB_IN: D175.2 (DIN), D179.4 (DOUT)
/KeyComma/RGB_OUT: D162.2 (DIN), D175.4 (DOUT)
/KeyControl/RGB_IN: D205.2 (DIN), D209.4 (DOUT)
/KeyControl/RGB_OUT: D198.2 (DIN), D205.4 (DOUT)
/KeyD/RGB_IN: D181.2 (DIN), D188.4 (DOUT)
/KeyD/RGB_OUT: D174.2 (DIN), D181.4 (DOUT)
/KeyDelete/RGB_IN: D195.4 (DOUT), D204.2 (DIN)
/KeyE/RGB_IN: D172.4 (DOUT), D183.2 (DIN)
/KeyE/RGB_OUT: D183.4 (DOUT), D189.2 (DIN)
/KeyEqual/RGB_IN: D185.4 (DOUT), D195.2 (DIN)
/KeyEsc/RGB_IN: D201.2 (DIN), D211.4 (DOUT)
/KeyF1/RGB_IN: D149.4 (DOUT), D154.2 (DIN)
/KeyF1/RGB_OUT: D154.4 (DOUT), D207.2 (DIN)
/KeyF2/RGB_OUT: D159.2 (DIN), D207.4 (DOUT)
/KeyF3/RGB_OUT: D159.4 (DOUT), D208.2 (DIN)
/KeyF4/RGB_OUT: D160.2 (DIN), D208.4 (DOUT)
/KeyF/RGB_OUT: D163.2 (DIN), D174.4 (DOUT)
/KeyFn/RGB_IN: D226.2 (DIN), D228.4 (DOUT)
/KeyG/RGB_OUT: D157.2 (DIN), D163.4 (DOUT)
/KeyH/RGB_OUT: D156.2 (DIN), D157.4 (DOUT)
/KeyHelp/RGB_OUT: D160.4 (DOUT), D214.2 (DIN)
/KeyI/RGB_IN: D166.2 (DIN), D171.4 (DOUT)
/KeyI/RGB_OUT: D152.2 (DIN), D166.4 (DOUT)
/KeyJ/RGB_OUT: D156.4 (DOUT), D164.2 (DIN)
/KeyK/RGB_OUT: D164.4 (DOUT), D173.2 (DIN)
/KeyL/RGB_OUT: D173.4 (DOUT), D182.2 (DIN)
/KeyLeftBracket/RGB_IN: D190.2 (DIN), D194.4 (DOUT)
/KeyLeftBracket/RGB_OUT: D180.2 (DIN), D190.4 (DOUT)
/KeyLeftShift/RGB_IN: D200.4 (DOUT), D209.2 (DIN)
/KeyM/RGB_OUT: D155.2 (DIN), D162.4 (DOUT)
/KeyO/RGB_IN: D171.2 (DIN), D180.4 (DOUT)
/KeyOption/RGB_IN: D212.2 (DIN), D213.4 (DOUT)
/KeyOption/RGB_OUT: D211.2 (DIN), D212.4 (DOUT)
/KeyPeriod/RGB_IN: D179.2 (DIN), D191.4 (DOUT)
/KeyQ/RGB_IN: D189.4 (DOUT), D199.2 (DIN)
/KeyQ/RGB_OUT: D199.4 (DOUT), D206.2 (DIN)
/KeyQuote/RGB_IN: D182.4 (DOUT), D192.2 (DIN)
/KeyQuote/RGB_OUT: D192.4 (DOUT), D203.2 (DIN)
/KeyR/RGB_IN: D165.4 (DOUT), D172.2 (DIN)
/KeyReturn/RGB_OUT: D203.4 (DOUT), D215.2 (DIN)
/KeyRightAlt/RGB_IN: D224.4 (DOUT), D228.2 (DIN)
/KeyRightShift/RGB_OUT: D191.2 (DIN), D215.4 (DOUT)
/KeySelect/RGB_IN: D213.2 (DIN), D214.4 (DOUT)
/KeySpace/RGB_IN: D158.2 (DIN), D222.4 (DOUT)
/KeySpace/RGB_OUT: D158.4 (DOUT), D223.2 (DIN)
/KeyT/RGB_IN: D153.4 (DOUT), D165.2 (DIN)
/KeyU/RGB_OUT: D152.4 (DOUT), D153.2 (DIN)
/KeyX/RGB_OUT: D187.4 (DOUT), D200.2 (DIN)
/Logo1/RGB_OUT: D216.4 (DOUT), D217.2 (DIN)
/Logo2/RGB_OUT: D217.4 (DOUT), D218.2 (DIN)
/Logo3/RGB_OUT: D218.4 (DOUT), D219.2 (DIN)
/Logo4/RGB_OUT: D219.4 (DOUT), D220.2 (DIN)
/Logo5/RGB_OUT: D149.2 (DIN), D220.4 (DOUT)
/Space1/RGB_OUT: D221.4 (DOUT), D222.2 (DIN)
/Space3/RGB_OUT: D223.4 (DOUT), D224.2 (DIN)
COL_1: SW10.1, SW11.1, SW12.1, SW13.1, SW14.1, SW15.1, SW19.1, TP1.1 (1_1), U7.11 (GPIO8)
COL_2: SW16.1, SW17.1, SW18.1, SW20.1, TP2.1 (1_1), U7.12 (GPIO9)
COL_3: SW21.1, SW22.1, SW23.1, SW24.1, SW25.1, SW26.1, SW27.1, SW28.1, TP3.1 (1_1), U7.13 (GPIO10)
COL_4: SW29.1, SW30.1, SW31.1, SW32.1, SW33.1, SW34.1, SW35.1, SW36.1, TP4.1 (1_1), U7.14 (GPIO11)
COL_5: SW37.1, SW38.1, SW39.1, SW40.1, SW41.1, SW42.1, SW43.1, SW44.1, TP5.1 (1_1), U7.15 (GPIO12)
COL_6: SW45.1, SW46.1, SW47.1, SW48.1, SW49.1, SW50.1, SW51.1, SW52.1, TP6.1 (1_1), U7.16 (GPIO13)
COL_7: SW53.1, SW54.1, SW55.1, SW56.1, SW57.1, SW58.1, SW59.1, TP7.1 (1_1), U7.17 (GPIO14)
COL_8: SW61.1, SW62.1, SW63.1, SW64.1, SW65.1, SW67.1, SW68.1, SW80.1, TP8.1 (1_1), U7.18 (GPIO15)
COL_9: SW66.1, SW69.1, SW70.1, SW75.1, SW76.1, SW77.1, SW78.1, SW79.1, TP9.1 (1_1), U7.27 (GPIO16)
CONSOLE: SW71.1, SW72.1, SW73.1, SW74.1, U7.28 (GPIO17)
EncoderA: SW1.A, U7.37 (GPIO25)
EncoderB: SW1.B, U7.36 (GPIO24)
EncoderSwitch: SW1.S1, U7.35 (GPIO23)
GND: C4.2, C5.2, C6.2, C7.2, C8.2, C9.2, C10.2, C11.2, C12.2, C13.2, C14.2, C24.2, C25.1, C27.2, C28.2, C42.2, C43.1, C75.2, C76.2, C77.2, C78.2, C79.2, C80.2, C81.2, C82.2, C83.2, C84.2, C85.2, C86.2, C87.2, C88.2, C89.2, C90.2, C91.2, C92.2, C93.2, C94.2, C95.2, C96.2, C97.2, C98.2, C99.2, C100.2, C101.2, C102.2, C103.2, C104.2, C105.2, C106.2, C107.2, C108.2, C109.2, C110.2, C111.2, C112.2, C113.2, C114.2, C115.2, C116.2, C117.2, C118.2, C119.2, C120.2, C121.2, C123.2, C124.2, C125.2, C126.2, C127.2, C128.2, C129.2, C130.2, C131.2, C132.2, C133.2, C134.2, C135.2, C136.2, C137.2, C138.2, C139.2, C140.2, C141.2, C142.2, C143.2, C144.2, C145.2, C146.2, C147.2, C148.2, C149.2, C150.2, C151.2, C152.2, C153.2, C154.2, C155.2, D149.1 (VSS), D150.1 (VSS), D151.1 (VSS), D152.1 (VSS), D153.1 (VSS), D154.1 (VSS), D155.1 (VSS), D156.1 (VSS), D157.1 (VSS), D158.1 (VSS), D159.1 (VSS), D160.1 (VSS), D161.1 (VSS), D162.1 (VSS), D163.1 (VSS), D164.1 (VSS), D165.1 (VSS), D166.1 (VSS), D167.1 (VSS), D168.1 (VSS), D169.1 (VSS), D170.1 (VSS), D171.1 (VSS), D172.1 (VSS), D173.1 (VSS), D174.1 (VSS), D175.1 (VSS), D176.1 (VSS), D177.1 (VSS), D178.1 (VSS), D179.1 (VSS), D180.1 (VSS), D181.1 (VSS), D182.1 (VSS), D183.1 (VSS), D184.1 (VSS), D185.1 (VSS), D186.1 (VSS), D187.1 (VSS), D188.1 (VSS), D189.1 (VSS), D190.1 (VSS), D191.1 (VSS), D192.1 (VSS), D193.1 (VSS), D194.1 (VSS), D195.1 (VSS), D197.1 (VSS), D198.1 (VSS), D199.1 (VSS), D200.1 (VSS), D201.1 (VSS), D202.1 (VSS), D203.1 (VSS), D204.1 (VSS), D205.1 (VSS), D206.1 (VSS), D207.1 (VSS), D208.1 (VSS), D209.1 (VSS), D210.1 (VSS), D211.1 (VSS), D212.1 (VSS), D213.1 (VSS), D214.1 (VSS), D215.1 (VSS), D216.1 (VSS), D217.1 (VSS), D218.1 (VSS), D219.1 (VSS), D220.1 (VSS), D221.1 (VSS), D222.1 (VSS), D223.1 (VSS), D224.1 (VSS), D225.1 (VSS), D226.1 (VSS), D227.1 (VSS), D228.1 (VSS), D229.1 (VSS), H1.1 (1_1), H2.1 (1_1), H3.1 (1_1), H4.1 (1_1), J1.4, J4.4, J5.A1 (GND), J5.A12 (GND), J5.B1 (GND), J5.B12 (GND), J5.S1 (SHIELD), J6.4, J9.2, J9.MP (MountPin), R6.2, R7.2, SW1.C, SW1.MP, SW1.S2, SW2.1, SW3.1, U4.1 (GND), U7.19 (TESTEN), U7.57 (GND), U9.4 (GND), X1.2, X1.4
unnamed: C25.2, R31.1, X1.3
unnamed: D17.2 (A), SW10.2
unnamed: D18.2 (A), SW11.2
unnamed: D19.2 (A), SW12.2
unnamed: D20.2 (A), SW13.2
unnamed: D21.2 (A), SW14.2
unnamed: D22.2 (A), SW15.2
unnamed: D23.2 (A), SW16.2
unnamed: D24.2 (A), SW17.2
unnamed: D25.2 (A), SW18.2
unnamed: D26.2 (A), SW19.2
unnamed: D27.2 (A), SW20.2
unnamed: D28.2 (A), SW21.2
unnamed: D29.2 (A), SW22.2
unnamed: D30.2 (A), SW23.2
unnamed: D31.2 (A), SW24.2
unnamed: D47.2 (A), SW25.2
unnamed: D49.2 (A), SW26.2
unnamed: D51.2 (A), SW27.2
unnamed: D53.2 (A), SW28.2
unnamed: D55.2 (A), SW29.2
unnamed: D57.2 (A), SW30.2
unnamed: D59.2 (A), SW31.2
unnamed: D61.2 (A), SW32.2
unnamed: D63.2 (A), SW33.2
unnamed: D65.2 (A), SW34.2
unnamed: D67.2 (A), SW35.2
unnamed: D69.2 (A), SW36.2
unnamed: D71.2 (A), SW37.2
unnamed: D73.2 (A), SW38.2
unnamed: D75.2 (A), SW39.2
unnamed: D77.2 (A), SW40.2
unnamed: D79.2 (A), SW41.2
unnamed: D81.2 (A), SW42.2
unnamed: D83.2 (A), SW43.2
unnamed: D85.2 (A), SW44.2
unnamed: D87.2 (A), SW45.2
unnamed: D89.2 (A), SW46.2
unnamed: D91.2 (A), SW47.2
unnamed: D93.2 (A), SW48.2
unnamed: D95.2 (A), SW49.2
unnamed: D97.2 (A), SW50.2
unnamed: D99.2 (A), SW51.2
unnamed: D101.2 (A), SW52.2
unnamed: D103.2 (A), SW53.2
unnamed: D105.2 (A), SW54.2
unnamed: D107.2 (A), SW55.2
unnamed: D109.2 (A), SW56.2
unnamed: D111.2 (A), SW57.2
unnamed: D113.2 (A), SW58.2
unnamed: D115.2 (A), SW59.2
unnamed: D119.2 (A), SW61.2
unnamed: D121.2 (A), SW62.2
unnamed: D123.2 (A), SW63.2
unnamed: D125.2 (A), SW64.2
unnamed: D127.2 (A), SW65.2
unnamed: D128.2 (A), SW80.2
unnamed: D129.2 (A), SW66.2
unnamed: D130.2 (A), SW76.2
unnamed: D131.2 (A), SW67.2
unnamed: D132.2 (A), SW78.2
unnamed: D133.2 (A), SW68.2
unnamed: D134.2 (A), SW79.2
unnamed: D135.2 (A), SW69.2
unnamed: D137.2 (A), SW70.2
unnamed: D139.2 (A), SW71.2
unnamed: D141.2 (A), SW72.2
unnamed: D143.2 (A), SW73.2
unnamed: D145.2 (A), SW74.2
unnamed: D147.2 (A), SW75.2
unnamed: D148.2 (A), SW77.2
unnamed: J5.A5 (CC1), R7.1
unnamed: J5.B5 (CC2), R6.1
unnamed: R32.2, SW3.2
unnamed: R32.1, U7.26 (RUN)
OPTION: D141.1 (K), U7.30 (GPIO19)
RESET: D139.1 (K), U7.29 (GPIO18)
RGB: D216.2 (DIN), U7.38 (GPIO26_ADC0)
ROW_1: D17.1 (K), D53.1 (K), D55.1 (K), D71.1 (K), D89.1 (K), D103.1 (K), D123.1 (K), D137.1 (K), TP10.1 (1_1), U7.2 (GPIO0)
ROW_2: D18.1 (K), D51.1 (K), D57.1 (K), D73.1 (K), D87.1 (K), D105.1 (K), D119.1 (K), D130.1 (K), TP11.1 (1_1), U7.3 (GPIO1)
ROW_3: D19.1 (K), D49.1 (K), D59.1 (K), D75.1 (K), D93.1 (K), D113.1 (K), D121.1 (K), D134.1 (K), TP12.1 (1_1), U7.4 (GPIO2)
ROW_4: D20.1 (K), D47.1 (K), D61.1 (K), D77.1 (K), D99.1 (K), D111.1 (K), D131.1 (K), D148.1 (K), TP13.1 (1_1), U7.5 (GPIO3)
ROW_5: D21.1 (K), D23.1 (K), D31.1 (K), D63.1 (K), D79.1 (K), D97.1 (K), D125.1 (K), D129.1 (K), TP14.1 (1_1), U7.6 (GPIO4)
ROW_6: D24.1 (K), D30.1 (K), D65.1 (K), D81.1 (K), D95.1 (K), D109.1 (K), D127.1 (K), D132.1 (K), TP15.1 (1_1), U7.7 (GPIO5)
ROW_7: D22.1 (K), D25.1 (K), D29.1 (K), D67.1 (K), D83.1 (K), D91.1 (K), D115.1 (K), D128.1 (K), D147.1 (K), TP16.1 (1_1), U7.8 (GPIO6)
ROW_8: D26.1 (K), D27.1 (K), D28.1 (K), D69.1 (K), D85.1 (K), D101.1 (K), D107.1 (K), D133.1 (K), D135.1 (K), TP17.1 (1_1), U7.9 (GPIO7)
SELECT: D143.1 (K), U7.31 (GPIO20)
START: D145.1 (K), U7.32 (GPIO21)
VSYS: C43.2, C75.1, C76.1, C77.1, C78.1, C79.1, C80.1, C81.1, C82.1, C83.1, C84.1, C85.1, C86.1, C87.1, C88.1, C89.1, C90.1, C91.1, C92.1, C93.1, C94.1, C95.1, C96.1, C97.1, C98.1, C99.1, C100.1, C101.1, C102.1, C103.1, C104.1, C105.1, C106.1, C107.1, C108.1, C109.1, C110.1, C111.1, C112.1, C113.1, C114.1, C115.1, C116.1, C117.1, C118.1, C119.1, C120.1, C121.1, C123.1, C124.1, C125.1, C126.1, C127.1, C128.1, C129.1, C130.1, C131.1, C132.1, C133.1, C134.1, C135.1, C136.1, C137.1, C138.1, C139.1, C140.1, C141.1, C142.1, C143.1, C144.1, C145.1, C146.1, C147.1, C148.1, C149.1, C150.1, C151.1, C152.1, C153.1, C154.1, C155.1, D149.3 (VDD), D150.3 (VDD), D151.3 (VDD), D152.3 (VDD), D153.3 (VDD), D154.3 (VDD), D155.3 (VDD), D156.3 (VDD), D157.3 (VDD), D158.3 (VDD), D159.3 (VDD), D160.3 (VDD), D161.3 (VDD), D162.3 (VDD), D163.3 (VDD), D164.3 (VDD), D165.3 (VDD), D166.3 (VDD), D167.3 (VDD), D168.3 (VDD), D169.3 (VDD), D170.3 (VDD), D171.3 (VDD), D172.3 (VDD), D173.3 (VDD), D174.3 (VDD), D175.3 (VDD), D176.3 (VDD), D177.3 (VDD), D178.3 (VDD), D179.3 (VDD), D180.3 (VDD), D181.3 (VDD), D182.3 (VDD), D183.3 (VDD), D184.3 (VDD), D185.3 (VDD), D186.3 (VDD), D187.3 (VDD), D188.3 (VDD), D189.3 (VDD), D190.3 (VDD), D191.3 (VDD), D192.3 (VDD), D193.3 (VDD), D194.3 (VDD), D195.3 (VDD), D197.3 (VDD), D198.3 (VDD), D199.3 (VDD), D200.3 (VDD), D201.3 (VDD), D202.3 (VDD), D203.3 (VDD), D204.3 (VDD), D205.3 (VDD), D206.3 (VDD), D207.3 (VDD), D208.3 (VDD), D209.3 (VDD), D210.3 (VDD), D211.3 (VDD), D212.3 (VDD), D213.3 (VDD), D214.3 (VDD), D215.3 (VDD), D216.3 (VDD), D217.3 (VDD), D218.3 (VDD), D219.3 (VDD), D220.3 (VDD), D221.3 (VDD), D222.3 (VDD), D223.3 (VDD), D224.3 (VDD), D225.3 (VDD), D226.3 (VDD), D227.3 (VDD), D228.3 (VDD), D229.3 (VDD), J4.1, J5.A4 (VBUS), J5.A9 (VBUS), J5.B4 (VBUS), J5.B9 (VBUS), U4.3 (VI)

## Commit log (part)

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2026-04-19 First commit, from 0.51 test production
2026-04-25 Added DVI output. Better test generator picture. Use 2 pins for 6 bit dac with 9 bit patterns.
2026-04-25 Removed unused sigma delta dac
2026-04-25 Trivial audio test
2026-04-25 Toggle PBI pins to test (all seem to check out on J5 and J8)
2026-05-01 Test SIO and joysticks with toggle. Tested FSMC->SRAM1/SRAM2
2026-05-01 First hello world. Tried toggling a pin then tried using FSMC to test SRAM. LSE startup takes a few seconds so disabled that for now.
2026-05-01 Remove build folder
2026-05-01 Added SIO MOTOR issue
2026-05-03 RTOS working to some degree: toggling IO on a thread, logging over UART and USB working with the hub.
2026-05-03 Added some good suggestions from Woj
2026-05-04 Changed message
2026-05-04 Added an FSMC memory tester
2026-05-04 Added memory test to build
2026-05-04 Outputs are not high impedance by default on STM. Use input for now and label pins. Otherwise we drive some pins that stop us programming the FPGA etc!
2026-05-04 Remove some logging
2026-05-04 SDRAM testingpll_video.cmp
2026-05-05 Disable memtest
2026-05-06 First contribution ;)
